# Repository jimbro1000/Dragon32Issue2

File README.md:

# DRAGON 32 CPU Issue 2 #

This project is a recreation of the SA2120 CPU Mainboard 
for the 1982 Dragon Data **Dragon 32**

Everything (excluding modifications) is taken from the SA2120
schematics. Component positioning is as close to the original
too. The DRAM positions are as close as possible to the 1982
board but in preference use 4164s instead and set the
memory configuration jumpers appropriately, this avoids 
transplanting a riser board to use the 16x16k configuration.
The 16x16k should still work of course...

The two ROMS will need to be sourced from original boards or an
adapter used to allow the use of modern, available EPROM or EEPROM
components

The variable resistor (RV1) and motor relay (RL1) are adjusted 
for modern, available components. The cartridge port is based
on a modern design but may still be hard to source

## Important - Read This Bit! ##

September 2023: **In the year since I started developing this board the 
availability of the MC6883P/74LS783N SAM chip has gone from "easy to 
find" to almost unobtainable. The only known and proven source is from
DragonPlus Electronics. Please make sure you can find one before starting 
your build**

There is work being done to create a replacement for the SAM chip
but this is yet to become available

The rarer (but ironically easier to buy) 74LS785 should work as
a substitute

## Caveat ##

The scans on the original SA2120 schematics are not always clear
and it has taken a fair amount of careful study to get everything
correct but there is no guarantee at this time that the board 
design is as intended

The values of passive components are taken from observation of
an original production board, in most cases those values do
match the schematics, but not always

Revision 2.3 of this board is in a genuinely usable state but
still with caveats

### Working ###

In the current state (2.3) basic operation is tested working on
CPU, RAM, Keyboard, Joystick and Video.

### Working with caveat ###

Audio appears to be good but not fully tested (given the joysticks
work and the board produces audio there isn't much to go wrong
here)

### Untested ###

Parallel port is untested in either mode beyond verifying signals
to the port are present

## Modifications ##
### Joysticks ###

The two joystick ports provide a second fire button capability
wired to consecutive keyboard rows, as per the Tandy CoCo. 
Unless a two button joystick is used this make no difference to
the operation of the computer. It also requires the use of 6-pin 
DIN sockets, these are pin compatible with the 5-pin originals
so a regular single button joystick can still be used.

The two extra buttons can also be disabled by omitting L3 and L4

### Parallel Port ###

An extra jumper has been introduced to bypass the logic inverter
on the STROBE line. When bypassed the parallel port should 
operate as a communication port for DRIVEWIRE. In effect this
enables the printer port to behave as a TTL serial connection. 
Speed is limited by software and raw clock speed.

### Memory Addressing ###

The board is configurable between 32k and 64k ram addressing
using jumper 13/14. Position 13 is for original 32k ram
configuration, position 14 is for an upgraded 64k ram. Note
that this then requires removal of some additional passive 
components and assumes that suitable 64k x 1 ram chips are 
fitted in IC1 to IC8.

Jumper 9/10 has been added for consistency with some of the
other early designs and for compatibility with the 64k
upgrade. It is important to avoid populating C50-57 when
using this option, along with C12, C58, C59 and R66.

See [World of Dragon: Dragon 32 - 64k Upgrade]
(http://archive.worldofdragon.org/index.php?title=Dragon_32_-_64K_Upgrade)

## Video ##

The Rev 2.1 board adds two (hidden) solder jumpers for adapting
the board to NTSC output. By default these have a bridge putting
the board in PAL mode so unless you want NTSC output there is
nothing to be done.

To change the configuration the bridge on both jumpers needs to be
cut and the option pads bridged with solder. This bypasses the
additional logic for video sync. The jumpers are JP15/16 and 
JP17/18, these are positioned below IC15 and IC12 respectively. 
The default position is marked.

To complete the change an NTSC adapter board needs to be fitted.
This piggybacks the 6847 position and adds in a suitable NTSC
video modulator. The output of the NTSC board goes to PL8, next
to the PAL colour crystal XL1.

In this configuration there is no need to fit a number of components:

* IC9
* IC10
* IC11
* IC14
* IC21
* IC22
* IC26
* IC27
* IC29
* IC30
* IC32
* C2
* C3
* C5
* C6
* C7
* C24
* C25
* C28
* C46
* C47
* C71
* R2
* R3
* R4
* R17
* R18
* R33
* R34
* R35
* R44
* XL1

## Substitutions ##

Many of the original components are simply unobtainable or
just very hard (and expensive) to locate. The transistors
will need modern substitutes as the BC141, BC212 and 2N2369
are all obsolete but thankfully these are fairly run-of-the-mill
transistors and shouldn't cause any particular issues

The video op-amp SFC2318D at position IC10 is especially
hard to find and this one component can easily double the
price of populating the board if an original is used...
I've identified a Harris HA-5111 as a likely candidate, it
is an audio op-amp rated for upto 40MHz so plenty of 
bandwitdh for a simple PAL/NTSC video signal. There are of 
course lots of other single channel op-amps out there in a 
dip-8 format but they tend to be expensive (as in *really*
expensive) possibly cheaper than a real 2318D but not by
much, some are stupidly expensive (nearly 100x that
2318D). The HA-5111 should be about £0.90

The CPU, PIAs and VDG are all fairly easy to obtain online
and possibly even new (MC6821s are still made and there
are lots of compatible alternatives). A and B rated components
should all be usable but make sure the processor is an "09e".
The Hitachi HD6309 is usable but may cause crashes in some
software due to lazy coding

The 4000 series logic chips are particularly tricky - some
have modern equivalents. The MC14053 and MC14050 can be
replaced with modern CD4000 series chips. The MC14529
was replaced with a CD4000 series logic chip but even that
is now obsolete with no valid replacement

The LM1889 is another hard to find chip but still reasonably
cheap online when found

The SAM and the two ROMs are genuinely unavailable except 
from donor boards but the ROMs can be replaced with 27C64
eproms fitted with a suitable conversion shim board.

### The Future ###

As these parts become harder to find it is inevitable that
replacements and redesigns will be needed. Abandoning the
original composite video output circuits and moving to a
(more) modern RGB or VGA output instead removes a big
chunk of the more troublesome hardware, notably the LM1889
and SFC2318 along with a number of other common logic chips.
If a composite output is still required an ADR724J can be
used to generate the necessary signal, all in one chip

A cheat replacement for the 6847 exists, using a raspberry
pi pico but this could easily be reduced even further an
FPGA (assuming such chips are readily available again)

The ROMs can be replaced with a single EPROM/EEPROM, even
opening up the option of switchable ROM images given the
size of a modern EPROM's addressable memory. I have a
mini conversion board that fits into a single socket with
a jumper to the E pin of the second socket. (see 
https://github.com/jimbro1000/Dragon32RomFix)

The one thing that isn't so quickly removed from the
equation is that MC14529 - a dual 4-channel data
selector. Onsemi and Harris used to made the CD4529
that replaced the original MC14529 and it is only fairly 
recently that the chip became obsolete so there is
stock out there but the chip is somewhat specialised and
as such really isnt easily substituted even with a modern
SMD package.

The most likely candidate here is to use a GAL chip to 
simulate the switching behaviour of the MC14529 combined
with discrete analogue switches (such as 74LVC1G3157). This
will necessitate a new board design or a plugin board to
match the pinout of the 4529 chip

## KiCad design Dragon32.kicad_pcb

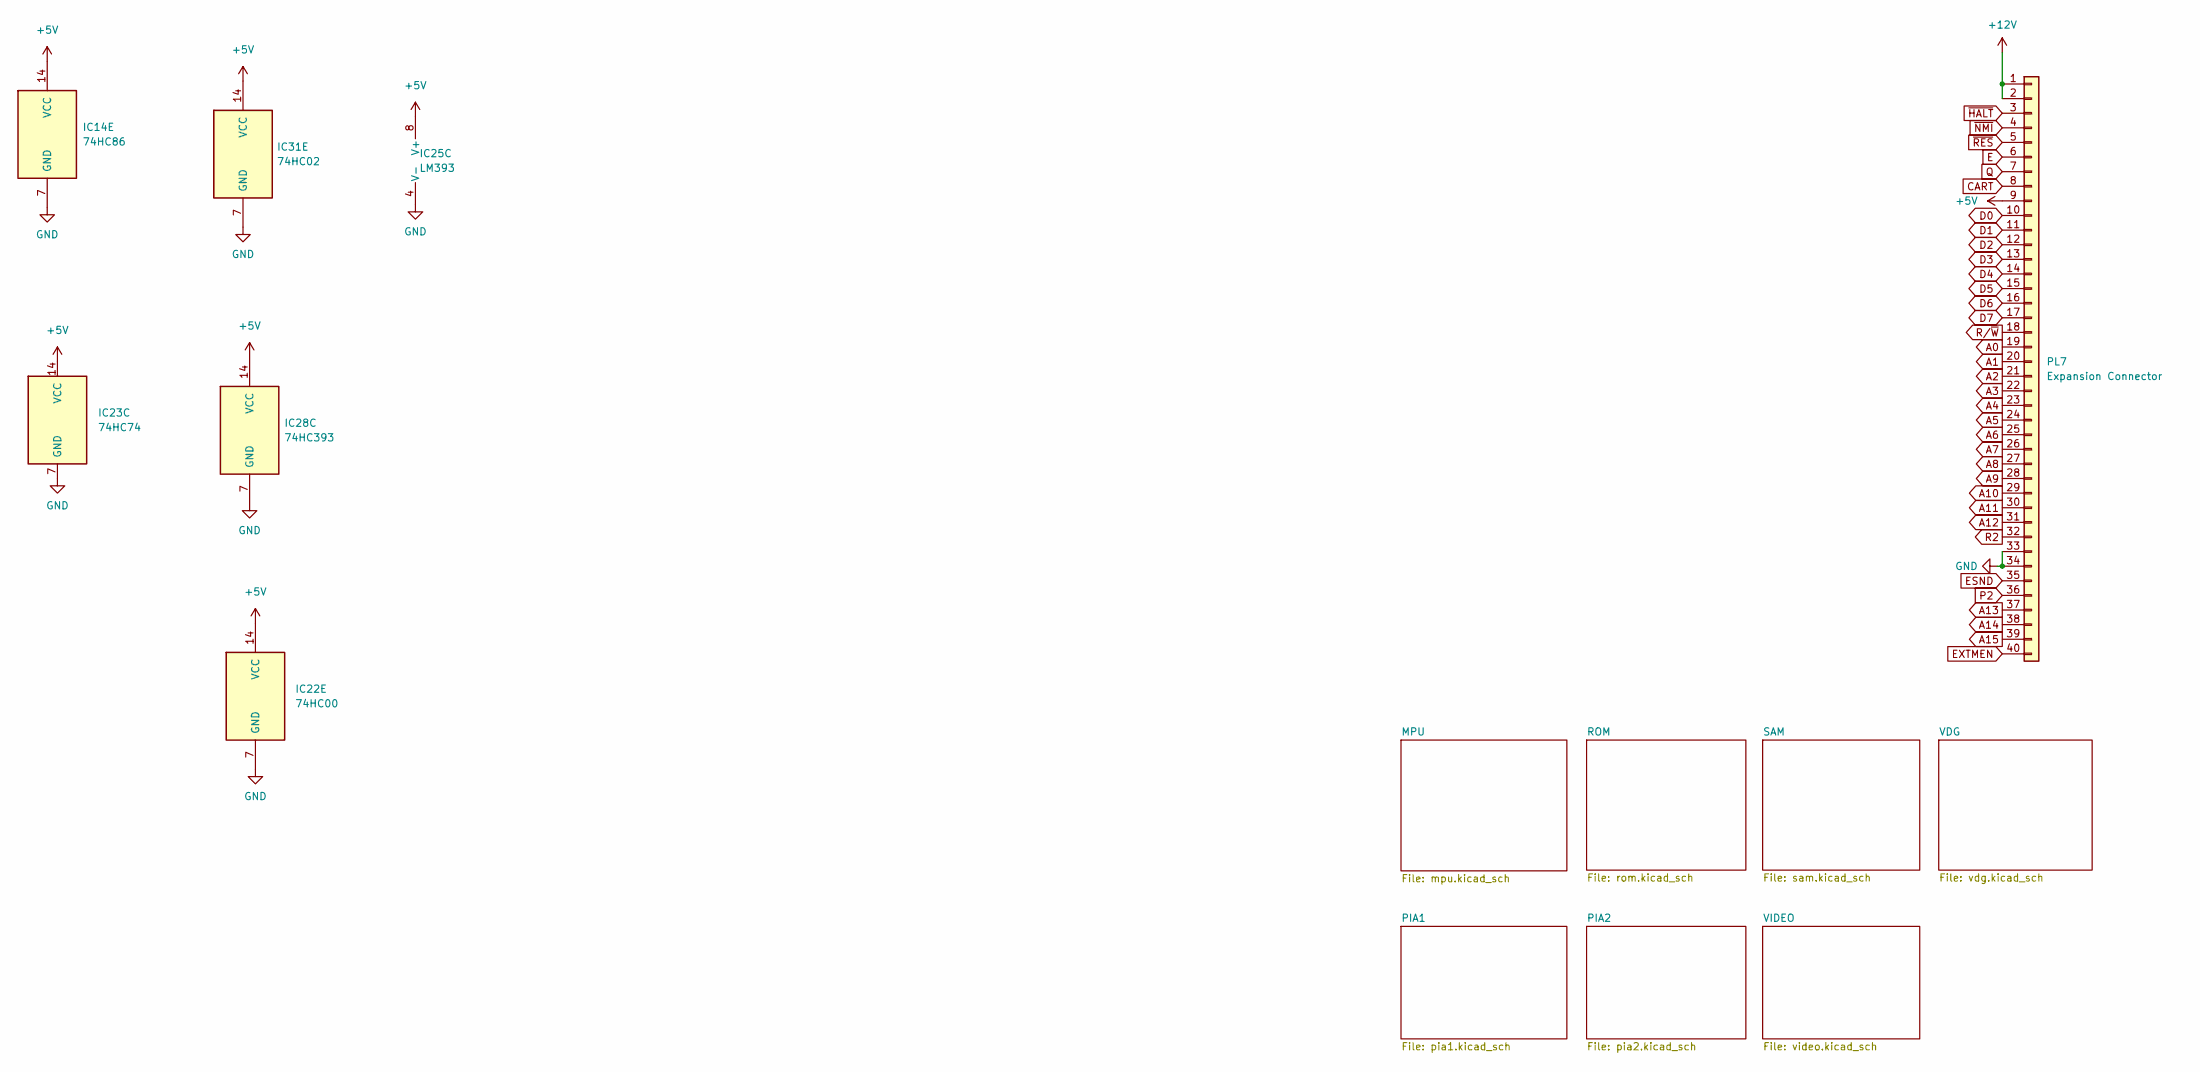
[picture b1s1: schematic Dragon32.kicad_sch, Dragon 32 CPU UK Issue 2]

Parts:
IC14: 74HC86; SOIC-14_3.9x8.7mm_P1.27mm
IC22: 74HC00; SOIC-14_3.9x8.7mm_P1.27mm
IC23: 74HC74; SOIC-14_3.9x8.7mm_P1.27mm
IC25: LM393; DIP-8_W7.62mm
IC28: 74HC393; SOIC-14_3.9x8.7mm_P1.27mm
IC31: 74HC02; SOIC-14_3.9x8.7mm_P1.27mm
PL7: Expansion Connector; Edge_2x20_P2.54mm_Horizontal

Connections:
+5V: IC14.14 (VCC), IC22.14 (VCC), IC23.14 (VCC), IC25.8 (V+), IC28.14 (VCC), IC31.14 (VCC), PL7.9; also elsewhere on the board
+12V: PL7.1, PL7.2; also elsewhere on the board
A0: PL7.19; also elsewhere on the board
A1: PL7.20; also elsewhere on the board
A2: PL7.21; also elsewhere on the board
A3: PL7.22; also elsewhere on the board
A4: PL7.23; also elsewhere on the board
A5: PL7.24; also elsewhere on the board
A6: PL7.25; also elsewhere on the board
A7: PL7.26; also elsewhere on the board
A8: PL7.27; also elsewhere on the board
A9: PL7.28; also elsewhere on the board
A10: PL7.29; also elsewhere on the board
A11: PL7.30; also elsewhere on the board
A12: PL7.31; also elsewhere on the board
A13: PL7.37; also elsewhere on the board
A14: PL7.38; also elsewhere on the board
A15: PL7.39; also elsewhere on the board
CART: PL7.8; also elsewhere on the board
D0: PL7.10; also elsewhere on the board
D1: PL7.11; also elsewhere on the board
D2: PL7.12; also elsewhere on the board
D3: PL7.13; also elsewhere on the board
D4: PL7.14; also elsewhere on the board
D5: PL7.15; also elsewhere on the board
D6: PL7.16; also elsewhere on the board
D7: PL7.17; also elsewhere on the board
E: PL7.6; also elsewhere on the board
ESND: PL7.35; also elsewhere on the board
EXTMEN: PL7.40; also elsewhere on the board
GND: IC14.7 (GND), IC22.7 (GND), IC23.7 (GND), IC25.4 (V-), IC28.7 (GND), IC31.7 (GND), PL7.33, PL7.34; also elsewhere on the board
P2: PL7.36; also elsewhere on the board
Q: PL7.7; also elsewhere on the board
R2: PL7.32; also elsewhere on the board
R/~W: PL7.18; also elsewhere on the board
~HALT: PL7.3; also elsewhere on the board
~NMI: PL7.4; also elsewhere on the board
~RES: PL7.5; also elsewhere on the board

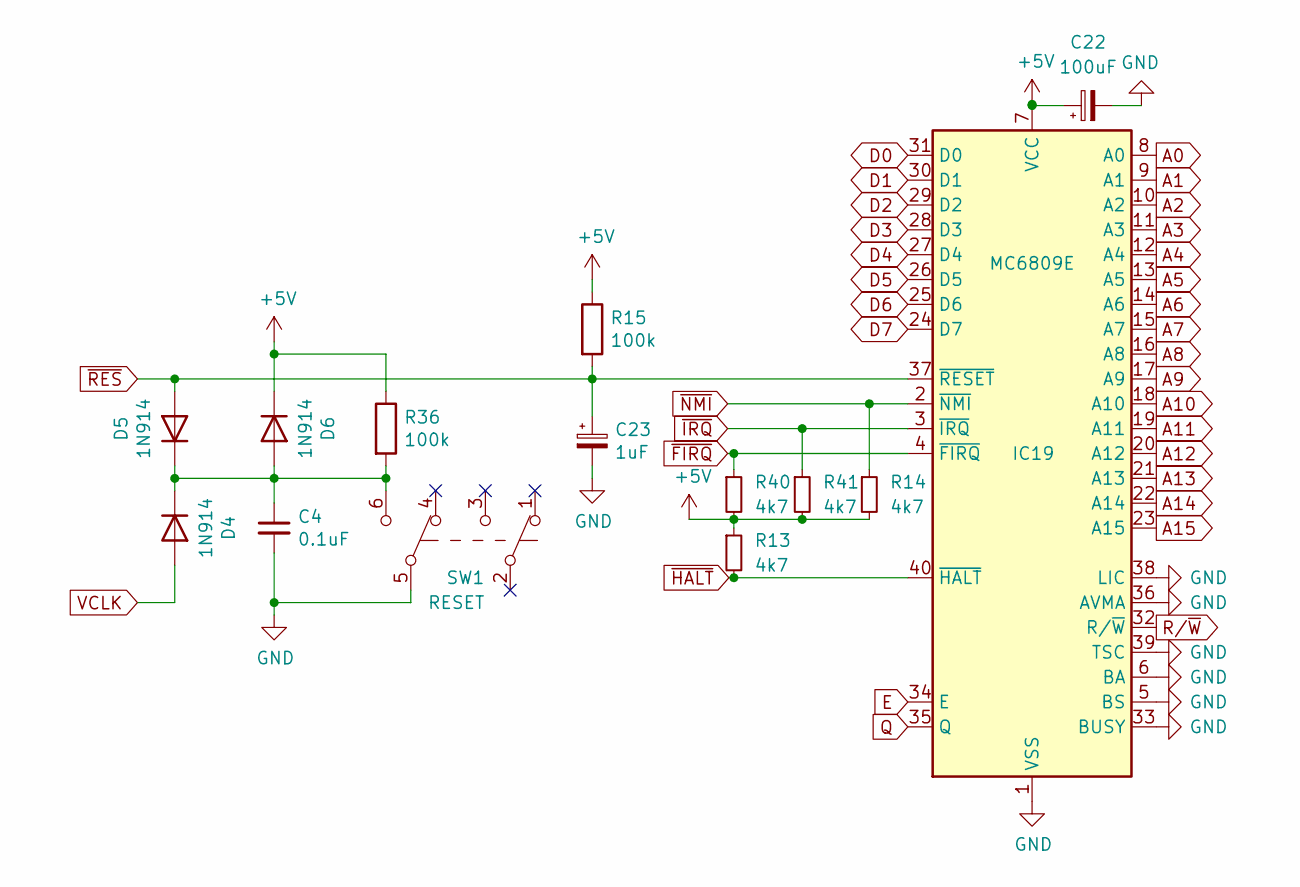
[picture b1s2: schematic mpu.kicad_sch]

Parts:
C4: 0.1uF; C_0805_2012Metric
C22: 100uF; CP_Elec_6.3x3.9
C23: 1uF; CP_Elec_5x3
D4, D5, D6: 1N914; D_0805_2012Metric
IC19: MC6809E; DIP-40_W15.24mm
R13, R14, R40, R41: 4k7; R_0805_2012Metric
R15, R36: 100k; R_0805_2012Metric
SW1: RESET; Button_AlpsAlpine_SPUN190900

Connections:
+5V: C22.1, D6.1 (K), IC19.7 (VCC), R13.1, R14.2, R15.1, R36.1, R40.2, R41.2; also elsewhere on the board
A0: IC19.8 (A0); also elsewhere on the board
A1: IC19.9 (A1); also elsewhere on the board
A2: IC19.10 (A2); also elsewhere on the board
A3: IC19.11 (A3); also elsewhere on the board
A4: IC19.12 (A4); also elsewhere on the board
A5: IC19.13 (A5); also elsewhere on the board
A6: IC19.14 (A6); also elsewhere on the board
A7: IC19.15 (A7); also elsewhere on the board
A8: IC19.16 (A8); also elsewhere on the board
A9: IC19.17 (A9); also elsewhere on the board
A10: IC19.18 (A10); also elsewhere on the board
A11: IC19.19 (A11); also elsewhere on the board
A12: IC19.20 (A12); also elsewhere on the board
A13: IC19.21 (A13); also elsewhere on the board
A14: IC19.22 (A14); also elsewhere on the board
A15: IC19.23 (A15); also elsewhere on the board
D0: IC19.31 (D0); also elsewhere on the board
D1: IC19.30 (D1); also elsewhere on the board
D2: IC19.29 (D2); also elsewhere on the board
D3: IC19.28 (D3); also elsewhere on the board
D4: IC19.27 (D4); also elsewhere on the board
D5: IC19.26 (D5); also elsewhere on the board
D6: IC19.25 (D6); also elsewhere on the board
D7: IC19.24 (D7); also elsewhere on the board
E: IC19.34 (E); also elsewhere on the board
GND: C4.2, C22.2, C23.2, IC19.1 (VSS), IC19.5 (BS), IC19.6 (BA), IC19.33 (BUSY), IC19.36 (AVMA), IC19.38 (LIC), IC19.39 (TSC), SW1.5 (B); also elsewhere on the board
unnamed: C4.1, D4.1 (K), D5.1 (K), D6.2 (A), R36.2, SW1.6 (C)
Q: IC19.35 (Q); also elsewhere on the board
R/~W: IC19.32 (R/~W); also elsewhere on the board
VCLK: D4.2 (A); also elsewhere on the board
~FIRQ: IC19.4 (~FIRQ), R40.1; also elsewhere on the board
~HALT: IC19.40 (~HALT), R13.2; also elsewhere on the board
~IRQ: IC19.3 (~IRQ), R41.1; also elsewhere on the board
~NMI: IC19.2 (~NMI), R14.1; also elsewhere on the board
~RES: C23.1, D5.2 (A), IC19.37 (~RESET), R15.2; also elsewhere on the board

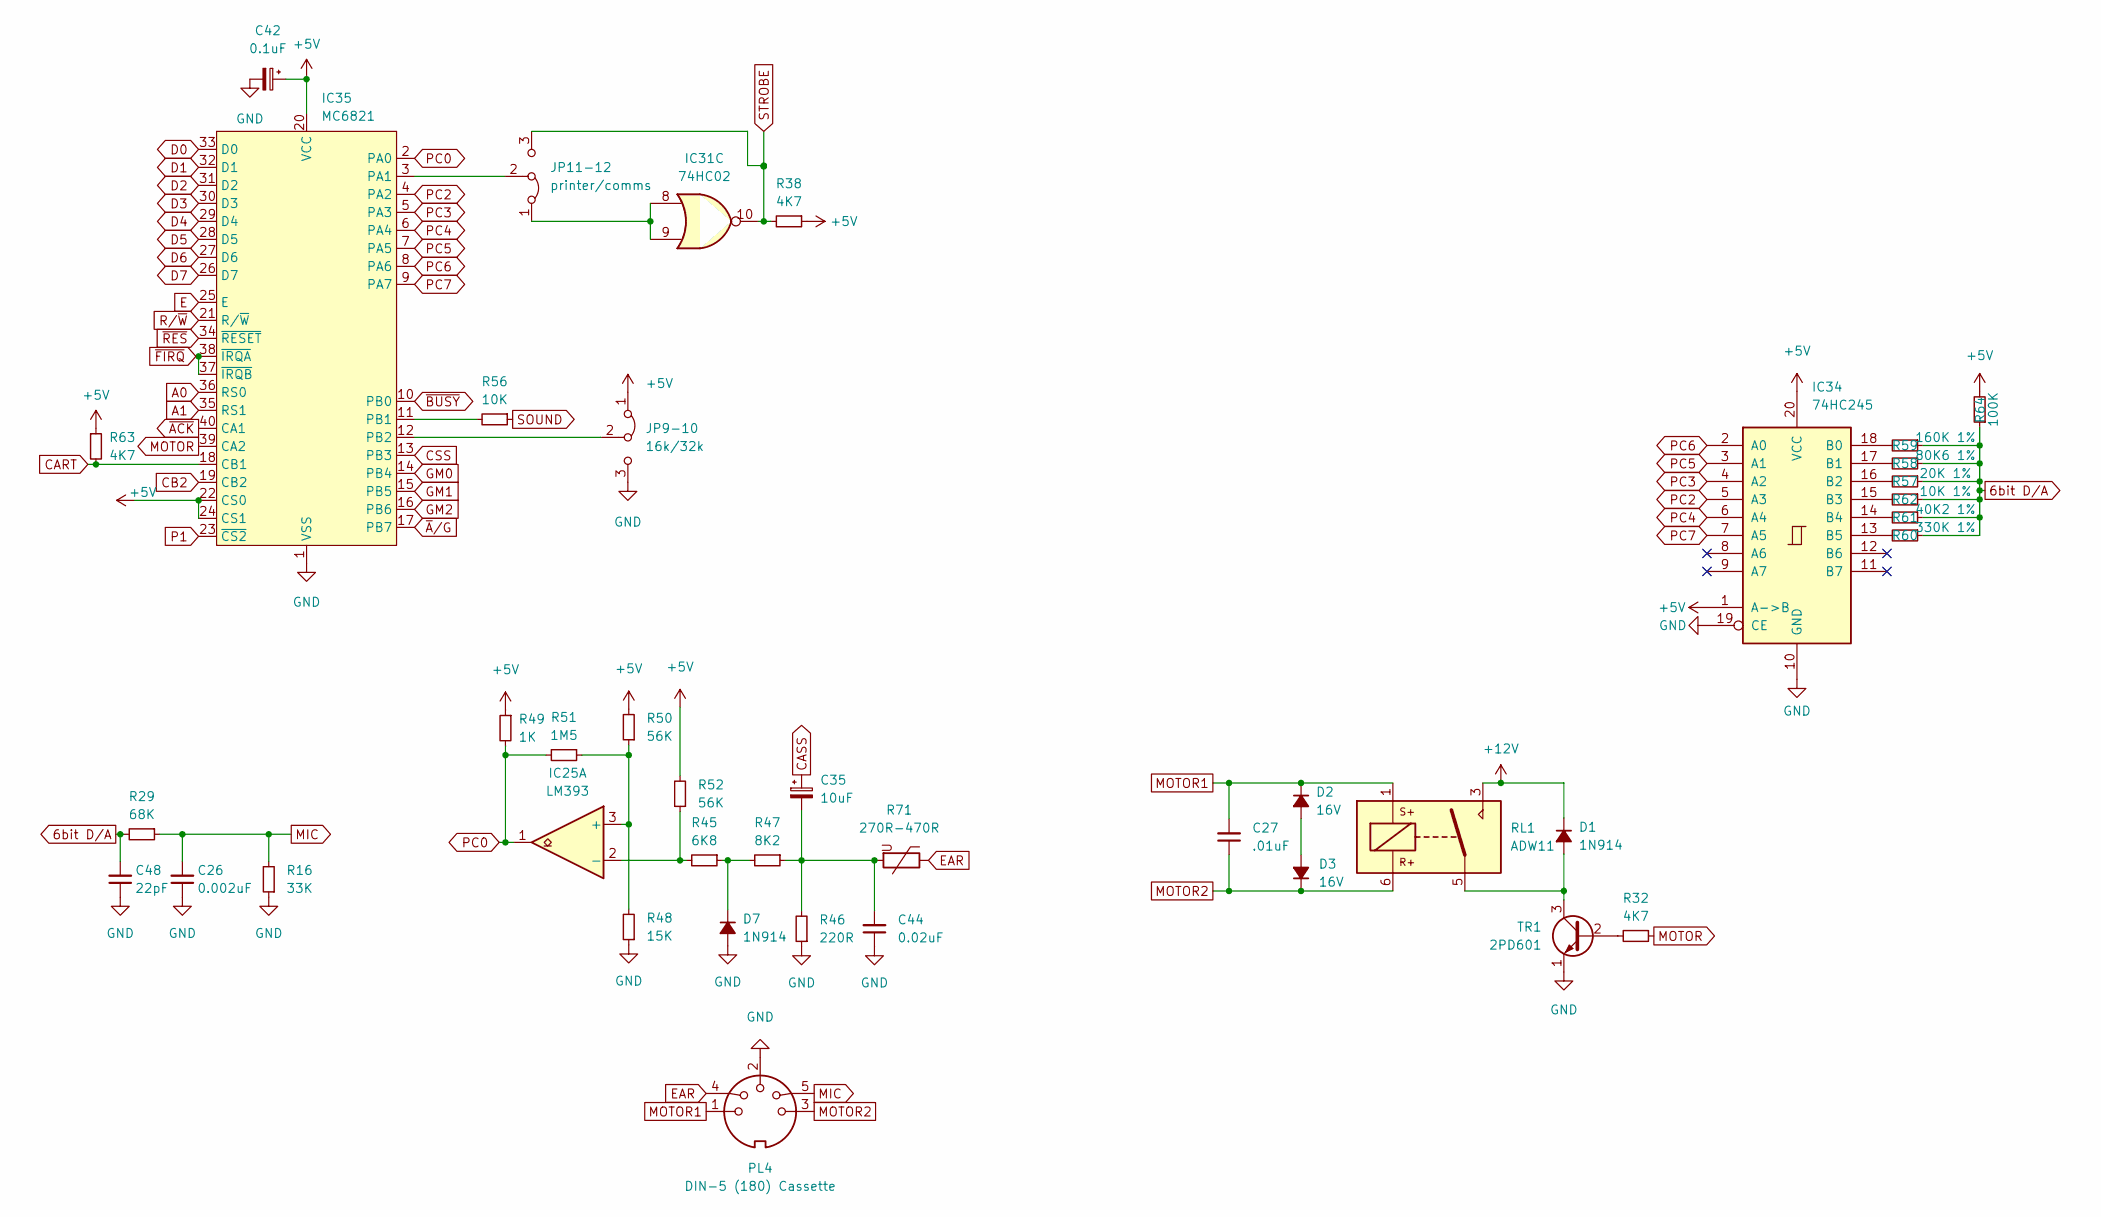
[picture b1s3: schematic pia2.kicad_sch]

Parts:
C26: 0.002uF; C_0805_2012Metric
C27: .01uF; C_0805_2012Metric
C35: 10uF; CP_Elec_5x3
C42: 0.1uF; CP_Elec_5x3
C44: 0.02uF; C_0805_2012Metric
C48: 22pF; C_0805_2012Metric
D1, D7: 1N914; D_0805_2012Metric
D2, D3: 16V; D_0805_2012Metric
IC25: LM393; DIP-8_W7.62mm
IC31: 74HC02; SOIC-14_3.9x8.7mm_P1.27mm
IC34: 74HC245; SOIC-20W_7.5x12.8mm_P1.27mm
IC35: MC6821; DIP-40_W15.24mm
JP9-10: 16k/32k; PinHeader_1x03_P2.54mm_Vertical
JP11-12: printer/comms; PinHeader_1x03_P2.54mm_Vertical
PL4: DIN-5 (180) Cassette; DIN-5_DELTRON_671-0501_45deg_Horizontal
R16: 33K; R_0805_2012Metric
R29: 68K; R_0805_2012Metric
R32, R38, R63: 4K7; R_0805_2012Metric
R45: 6K8; R_0805_2012Metric
R46: 220R; R_0805_2012Metric
R47: 8K2; R_0805_2012Metric
R48: 15K; R_0805_2012Metric
R49: 1K; R_0805_2012Metric
R50, R52: 56K; R_0805_2012Metric
R51: 1M5; R_0805_2012Metric
R56: 10K; R_0805_2012Metric
R57: 20K 1%; R_0805_2012Metric
R58: 80K6 1%; R_0805_2012Metric
R59: 160K 1%; R_0805_2012Metric
R60: 330K 1%; R_0805_2012Metric
R61: 40K2 1%; R_0805_2012Metric
R62: 10K 1%; R_0805_2012Metric
R64: 100K; R_0805_2012Metric
R71: 270R-470R; RV_Disc_D7mm_W3.4mm_P5mm
RL1: ADW11; Relay_1P1T_NO_10x24x18.8mm_Panasonic_ADW11xxxxW_THT
TR1: 2PD601; SOT-23

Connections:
6bit D/A: C48.2, R29.2, R57.1, R58.1, R59.1, R60.1, R61.1, R62.1, R64.1; also elsewhere on the board
+5V: C42.1, IC34.1 (A->B), IC34.20 (VCC), IC35.20 (VCC), IC35.22 (CS0), IC35.24 (CS1), JP9-10.1 (A), R38.1, R49.1, R50.2, R52.2, R63.1, R64.2; also elsewhere on the board
+12V: D1.1 (K), RL1.3; also elsewhere on the board
A0: IC35.36 (RS0); also elsewhere on the board
A1: IC35.35 (RS1); also elsewhere on the board
CART: IC35.18 (CB1), R63.2; also elsewhere on the board
CASS: C35.1; also elsewhere on the board
CB2: IC35.19 (CB2)
CSS: IC35.13 (PB3); also elsewhere on the board
D0: IC35.33 (D0); also elsewhere on the board
D1: IC35.32 (D1); also elsewhere on the board
D2: IC35.31 (D2); also elsewhere on the board
D3: IC35.30 (D3); also elsewhere on the board
D4: IC35.29 (D4); also elsewhere on the board
D5: IC35.28 (D5); also elsewhere on the board
D6: IC35.27 (D6); also elsewhere on the board
D7: IC35.26 (D7); also elsewhere on the board
E: IC35.25 (E); also elsewhere on the board
EAR: PL4.4, R71.1
GM0: IC35.14 (PB4); also elsewhere on the board
GM1: IC35.15 (PB5); also elsewhere on the board
GM2: IC35.16 (PB6); also elsewhere on the board
GND: C26.1, C42.2, C44.1, C48.1, D7.2 (A), IC34.10 (GND), IC34.19 (CE), IC35.1 (VSS), JP9-10.3 (B), PL4.2, R16.1, R46.1, R48.1, TR1.1 (E); also elsewhere on the board
MIC: C26.2, PL4.5, R16.2, R29.1
MOTOR: IC35.39 (CA2), R32.1
MOTOR1: C27.2, D2.1 (K), PL4.1, RL1.1
MOTOR2: C27.1, D3.1 (K), PL4.3, RL1.6
unnamed: C35.2, C44.2, R46.2, R47.1, R71.2
unnamed: D1.2 (A), RL1.5, TR1.3 (C)
unnamed: D2.2 (A), D3.2 (A)
unnamed: D7.1 (K), R45.1, R47.2
unnamed: IC25.2 (-), R45.2, R52.1
unnamed: IC25.3 (+), R48.2, R50.1, R51.1
unnamed: IC31.8, IC31.9, JP11-12.1 (A)
unnamed: IC34.13 (B5), R60.2
unnamed: IC34.14 (B4), R61.2
unnamed: IC34.15 (B3), R62.2
unnamed: IC34.16 (B2), R57.2
unnamed: IC34.17 (B1), R58.2
unnamed: IC34.18 (B0), R59.2
unnamed: IC35.3 (PA1), JP11-12.2 (C)
unnamed: IC35.11 (PB1), R56.2
unnamed: IC35.12 (PB2), JP9-10.2 (C)
unnamed: R32.2, TR1.2 (B)
P1: IC35.23 (~CS2); also elsewhere on the board
PC0: IC25.1, IC35.2 (PA0), R49.2, R51.2
PC2: IC34.5 (A3), IC35.4 (PA2)
PC3: IC34.4 (A2), IC35.5 (PA3)
PC4: IC34.6 (A4), IC35.6 (PA4)
PC5: IC34.3 (A1), IC35.7 (PA5)
PC6: IC34.2 (A0), IC35.8 (PA6)
PC7: IC34.7 (A5), IC35.9 (PA7)
R/~W: IC35.21 (R/~W); also elsewhere on the board
SOUND: R56.1; also elsewhere on the board
STROBE: IC31.10, JP11-12.3 (B), R38.2; also elsewhere on the board
~ACK: IC35.40 (CA1); also elsewhere on the board
~A/G: IC35.17 (PB7); also elsewhere on the board
~BUSY: IC35.10 (PB0); also elsewhere on the board
~FIRQ: IC35.37 (~IRQB), IC35.38 (~IRQA); also elsewhere on the board
~RES: IC35.34 (~RESET); also elsewhere on the board

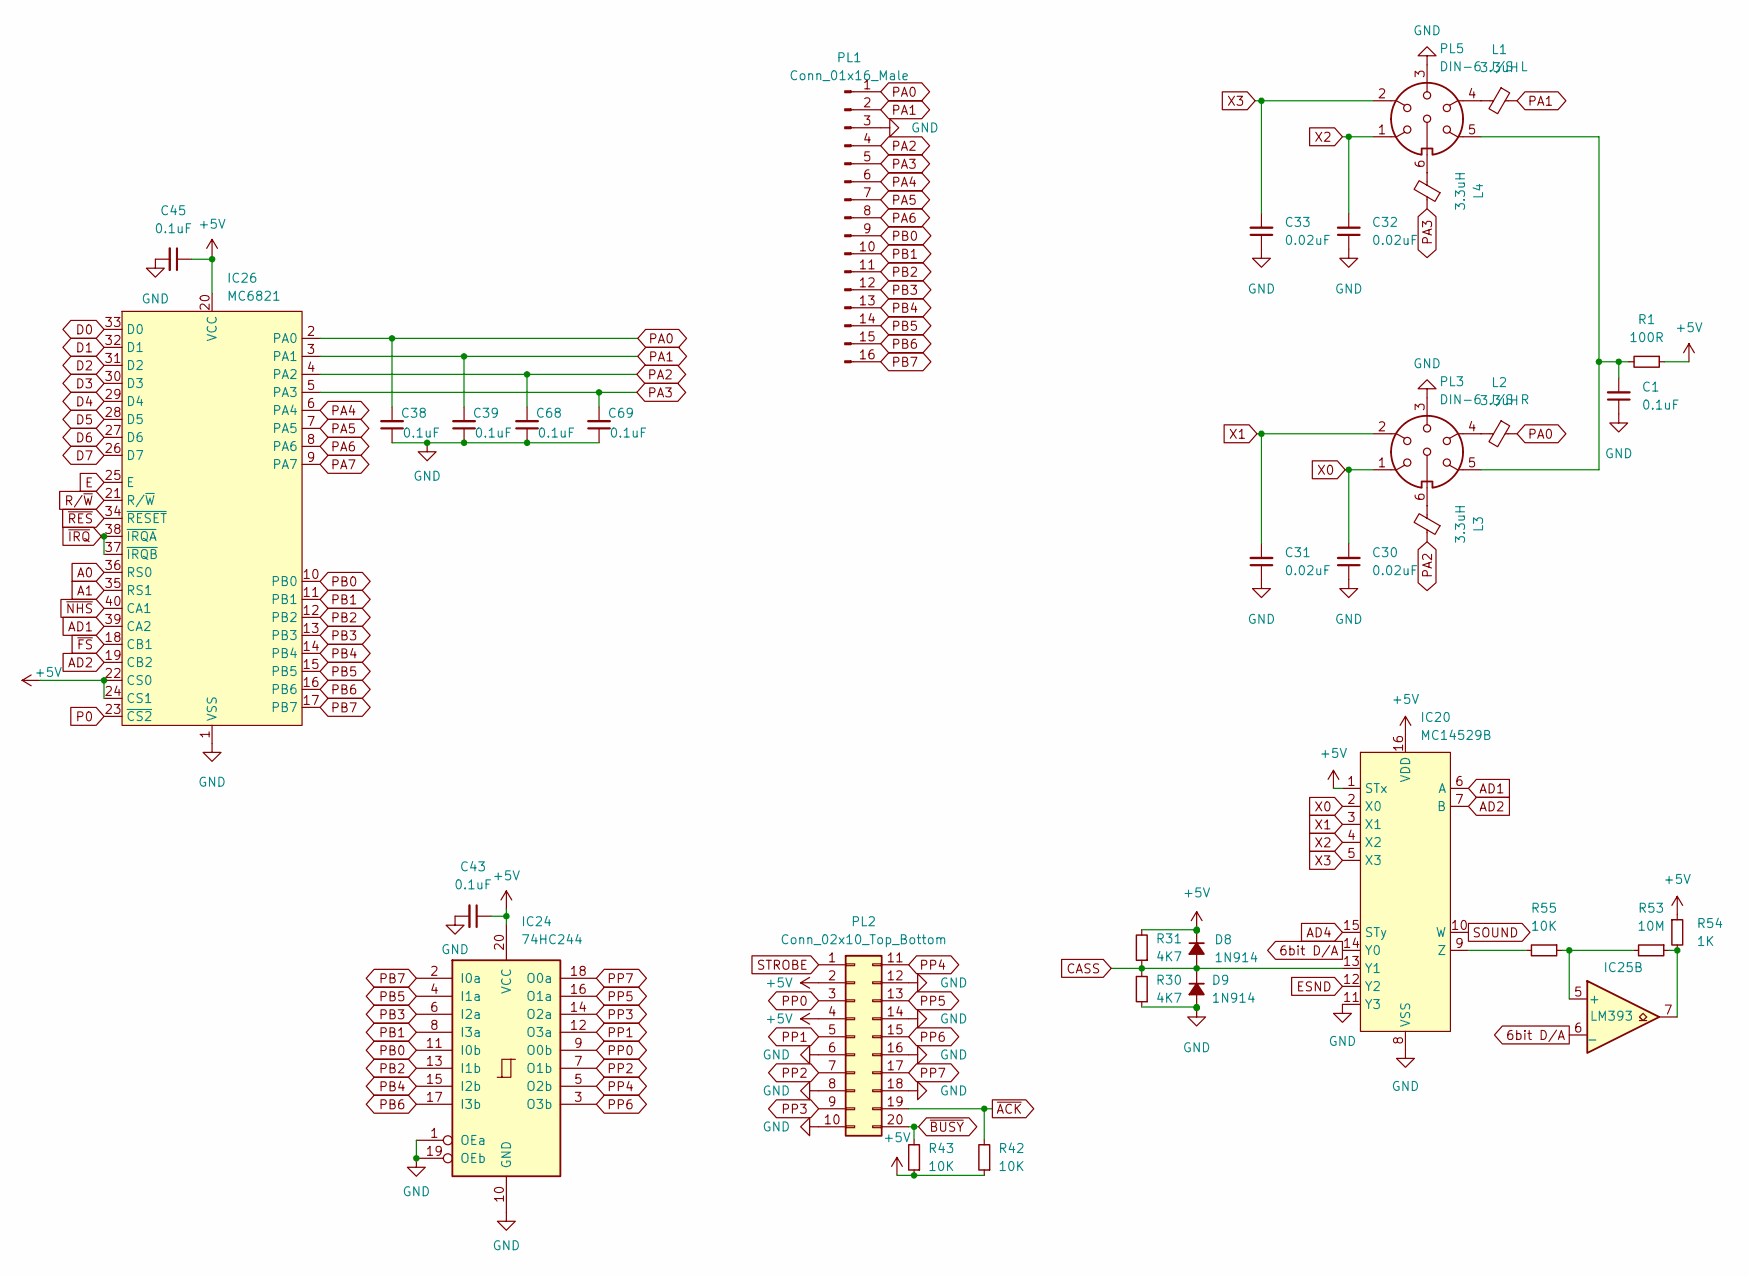
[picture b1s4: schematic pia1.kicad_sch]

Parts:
C1, C38, C39, C43, C45, C68, C69: 0.1uF; C_0805_2012Metric
C30, C31, C32, C33: 0.02uF; C_0805_2012Metric
D8, D9: 1N914; D_0805_2012Metric
IC20: MC14529B; DIP-16_W7.62mm
IC24: 74HC244; SOIC-20W_7.5x12.8mm_P1.27mm
IC25: LM393; DIP-8_W7.62mm
IC26: MC6821; DIP-40_W15.24mm
L1, L2, L3, L4: 3.3uH; L_Axial_L7.0mm_D3.3mm_P10.16mm_Horizontal_Fastron_MICC
PL1: Conn_01x16_Male; PinHeader_1x16_P2.54mm_Vertical
PL2: Conn_02x10_Top_Bottom; IDC-Header_2x10-1MP_P2.54mm_Latch_Horizontal
PL3: DIN-6 J/S R; DIN-6_DELTRON_671-0601_Horizontal
PL5: DIN-6 J/S L; DIN-6_DELTRON_671-0601_Horizontal
R1: 100R; R_0805_2012Metric
R30, R31: 4K7; R_0805_2012Metric
R42, R43, R55: 10K; R_0805_2012Metric
R53: 10M; R_0805_2012Metric
R54: 1K; R_0805_2012Metric

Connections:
6bit D/A: IC20.14 (Y0), IC25.6 (_); also elsewhere on the board
+5V: C43.1, C45.1, D8.1 (K), IC20.1 (STx), IC20.16 (VDD), IC24.20 (VCC), IC26.20 (VCC), IC26.22 (CS0), IC26.24 (CS1), PL2.2, PL2.4, R1.1, R31.2, R42.1, R43.1, R54.1; also elsewhere on the board
A0: IC26.36 (RS0); also elsewhere on the board
A1: IC26.35 (RS1); also elsewhere on the board
AD1: IC20.6 (A), IC26.39 (CA2)
AD2: IC20.7 (B), IC26.19 (CB2)
AD4: IC20.15 (STy)
CASS: D8.2 (A), D9.1 (K), IC20.13 (Y1), R30.2, R31.1; also elsewhere on the board
D0: IC26.33 (D0); also elsewhere on the board
D1: IC26.32 (D1); also elsewhere on the board
D2: IC26.31 (D2); also elsewhere on the board
D3: IC26.30 (D3); also elsewhere on the board
D4: IC26.29 (D4); also elsewhere on the board
D5: IC26.28 (D5); also elsewhere on the board
D6: IC26.27 (D6); also elsewhere on the board
D7: IC26.26 (D7); also elsewhere on the board
E: IC26.25 (E); also elsewhere on the board
ESND: IC20.12 (Y2); also elsewhere on the board
GND: C1.1, C30.1, C31.1, C32.1, C33.1, C38.1, C39.1, C43.2, C45.2, C68.1, C69.1, D9.2 (A), IC20.8 (VSS), IC20.11 (Y3), IC24.1 (OEa), IC24.10 (GND), IC24.19 (OEb), IC26.1 (VSS), PL1.3, PL2.6, PL2.8, PL2.10, PL2.12, PL2.14, PL2.16, PL2.18, PL3.3, PL5.3, R30.1; also elsewhere on the board
unnamed: C1.2, PL3.5, PL5.5, R1.2
unnamed: IC20.9 (Z), R55.2
unnamed: IC25.5 (+), R53.2, R55.1
unnamed: IC25.7, R53.1, R54.2
unnamed: L1.2, PL5.4
unnamed: L2.2, PL3.4
unnamed: L3.2, PL3.6
unnamed: L4.2, PL5.6
P0: IC26.23 (~CS2); also elsewhere on the board
PA0: C38.2, IC26.2 (PA0), L2.1, PL1.1
PA1: C39.2, IC26.3 (PA1), L1.1, PL1.2
PA2: C68.2, IC26.4 (PA2), L3.1, PL1.4
PA3: C69.2, IC26.5 (PA3), L4.1, PL1.5
PA4: IC26.6 (PA4), PL1.6
PA5: IC26.7 (PA5), PL1.7
PA6: IC26.8 (PA6), PL1.8
PA7: IC26.9 (PA7)
PB0: IC24.11 (I0b), IC26.10 (PB0), PL1.9
PB1: IC24.8 (I3a), IC26.11 (PB1), PL1.10
PB2: IC24.13 (I1b), IC26.12 (PB2), PL1.11
PB3: IC24.6 (I2a), IC26.13 (PB3), PL1.12
PB4: IC24.15 (I2b), IC26.14 (PB4), PL1.13
PB5: IC24.4 (I1a), IC26.15 (PB5), PL1.14
PB6: IC24.17 (I3b), IC26.16 (PB6), PL1.15
PB7: IC24.2 (I0a), IC26.17 (PB7), PL1.16
PP0: IC24.9 (O0b), PL2.3
PP1: IC24.12 (O3a), PL2.5
PP2: IC24.7 (O1b), PL2.7
PP3: IC24.14 (O2a), PL2.9
PP4: IC24.5 (O2b), PL2.11
PP5: IC24.16 (O1a), PL2.13
PP6: IC24.3 (O3b), PL2.15
PP7: IC24.18 (O0a), PL2.17
R/~W: IC26.21 (R/~W); also elsewhere on the board
SOUND: IC20.10 (W); also elsewhere on the board
STROBE: PL2.1; also elsewhere on the board
X0: C30.2, IC20.2 (X0), PL3.1
X1: C31.2, IC20.3 (X1), PL3.2
X2: C32.2, IC20.4 (X2), PL5.1
X3: C33.2, IC20.5 (X3), PL5.2
~ACK: PL2.19, R42.2; also elsewhere on the board
~BUSY: PL2.20, R43.2; also elsewhere on the board
~FS: IC26.18 (CB1); also elsewhere on the board
~IRQ: IC26.37 (~IRQB), IC26.38 (~IRQA); also elsewhere on the board
~NHS: IC26.40 (CA1); also elsewhere on the board
~RES: IC26.34 (~RESET); also elsewhere on the board

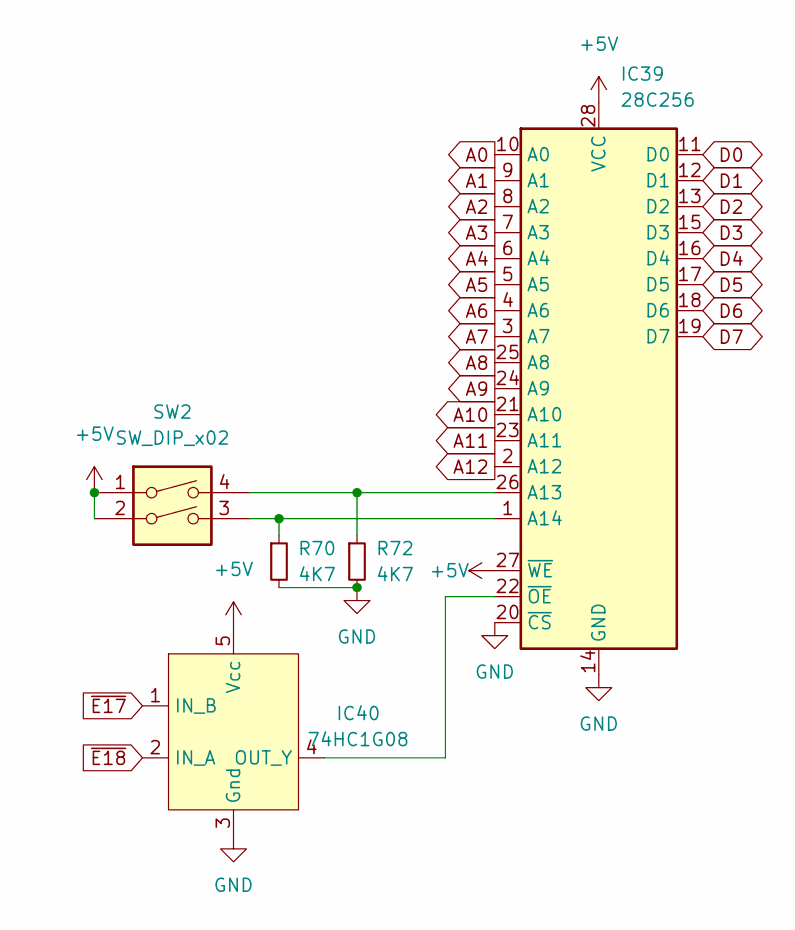
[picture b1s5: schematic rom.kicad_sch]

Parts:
IC39: 28C256; DIP-28_W15.24mm
IC40: 74HC1G08; TSOP-5_1.65x3.05mm_P0.95mm
R70, R72: 4K7; R_0805_2012Metric
SW2: SW_DIP_x02; DIP-4_W7.62mm

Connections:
+5V: IC39.27 (~WE), IC39.28 (VCC), IC40.5 (Vcc), SW2.1, SW2.2; also elsewhere on the board
A0: IC39.10 (A0); also elsewhere on the board
A1: IC39.9 (A1); also elsewhere on the board
A2: IC39.8 (A2); also elsewhere on the board
A3: IC39.7 (A3); also elsewhere on the board
A4: IC39.6 (A4); also elsewhere on the board
A5: IC39.5 (A5); also elsewhere on the board
A6: IC39.4 (A6); also elsewhere on the board
A7: IC39.3 (A7); also elsewhere on the board
A8: IC39.25 (A8); also elsewhere on the board
A9: IC39.24 (A9); also elsewhere on the board
A10: IC39.21 (A10); also elsewhere on the board
A11: IC39.23 (A11); also elsewhere on the board
A12: IC39.2 (A12); also elsewhere on the board
D0: IC39.11 (D0); also elsewhere on the board
D1: IC39.12 (D1); also elsewhere on the board
D2: IC39.13 (D2); also elsewhere on the board
D3: IC39.15 (D3); also elsewhere on the board
D4: IC39.16 (D4); also elsewhere on the board
D5: IC39.17 (D5); also elsewhere on the board
D6: IC39.18 (D6); also elsewhere on the board
D7: IC39.19 (D7); also elsewhere on the board
GND: IC39.14 (GND), IC39.20 (~CS), IC40.3 (Gnd), R70.2, R72.2; also elsewhere on the board
unnamed: IC39.1 (A14), R70.1, SW2.3
unnamed: IC39.22 (~OE), IC40.4 (OUT_Y)
unnamed: IC39.26 (A13), R72.1, SW2.4
~E17: IC40.1 (IN_B); also elsewhere on the board
~E18: IC40.2 (IN_A); also elsewhere on the board

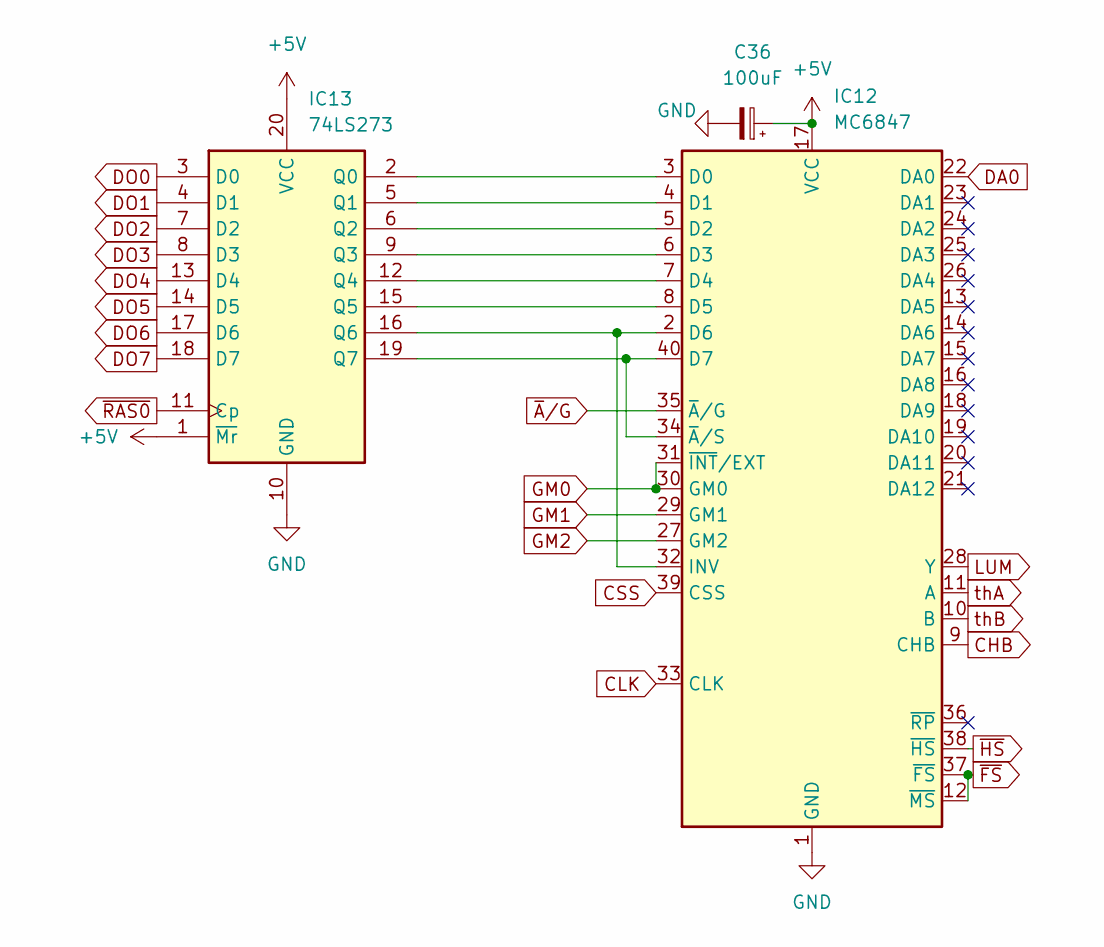
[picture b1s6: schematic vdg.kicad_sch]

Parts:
C36: 100uF; CP_Elec_8x5.4
IC12: MC6847; DIP-40_W15.24mm
IC13: 74LS273; DIP-20_W7.62mm

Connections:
+5V: C36.1, IC12.17 (VCC), IC13.1 (~Mr), IC13.20 (VCC); also elsewhere on the board
CHB: IC12.9 (CHB); also elsewhere on the board
CLK: IC12.33 (CLK); also elsewhere on the board
CSS: IC12.39 (CSS); also elsewhere on the board
DA0: IC12.22 (DA0); also elsewhere on the board
DO0: IC13.3 (D0); also elsewhere on the board
DO1: IC13.4 (D1); also elsewhere on the board
DO2: IC13.7 (D2); also elsewhere on the board
DO3: IC13.8 (D3); also elsewhere on the board
DO4: IC13.13 (D4); also elsewhere on the board
DO5: IC13.14 (D5); also elsewhere on the board
DO6: IC13.17 (D6); also elsewhere on the board
DO7: IC13.18 (D7); also elsewhere on the board
GM0: IC12.30 (GM0), IC12.31 (~INT/EXT); also elsewhere on the board
GM1: IC12.29 (GM1); also elsewhere on the board
GM2: IC12.27 (GM2); also elsewhere on the board
GND: C36.2, IC12.1 (GND), IC13.10 (GND); also elsewhere on the board
LUM: IC12.28 (Y); also elsewhere on the board
unnamed: IC12.2 (D6), IC12.32 (INV), IC13.16 (Q6)
unnamed: IC12.3 (D0), IC13.2 (Q0)
unnamed: IC12.4 (D1), IC13.5 (Q1)
unnamed: IC12.5 (D2), IC13.6 (Q2)
unnamed: IC12.6 (D3), IC13.9 (Q3)
unnamed: IC12.7 (D4), IC13.12 (Q4)
unnamed: IC12.8 (D5), IC13.15 (Q5)
unnamed: IC12.34 (~A/S), IC12.40 (D7), IC13.19 (Q7)
thA: IC12.11 (A); also elsewhere on the board
thB: IC12.10 (B); also elsewhere on the board
~A/G: IC12.35 (~A/G); also elsewhere on the board
~FS: IC12.12 (~MS), IC12.37 (~FS); also elsewhere on the board
~HS: IC12.38 (~HS); also elsewhere on the board
~RAS0: IC13.11 (Cp); also elsewhere on the board
